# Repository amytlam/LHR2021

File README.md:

# LHR2021
This is the repository for the files associated with the paper "DIY Liquid Handling Robots for Integrated STEM Education and Life-Science Research".

This includes the following:
1. Hardware documentation:
    - Parts list
    - CAD source designs for mechanical parts
    - Laser cutting fabrication files (5 sheets)
    - Fabrication files for 3D printed parts
    - Electronic circuit schematic diagrams and CAD files
    - Assembly instructions
2. Software:
    - Low-level control software for Arduino
    - Python API and tools for tuning and calibration
    - Snap4Arduino visual programming environment

## Contents

The `hardware/` directory of this repository contains fabrication files and documentation for all hardware for the three-axis robot. CAD source designs for the mechanical components and subassemblies of the robot can be found in an associated [Onshape project](https://cad.onshape.com/documents/6f3ff9e60612f07463807b51/w/7c9831bb106114d48918156b/e/005c0d1900650c2e45e341be?renderMode=0&uiState=6254cec2aa34676ff2f642a7), which is made public for copying and exporting. These source designs were exported to create the cut patterns in `hardware/laser_cut_CAD_files/` and the 3D printing files in `hardware/3d_printed_CAD_files/`.

Source code and overview-level documentation of all software can be found at the associated repository [github.com/ethanjli/liquid-handling-robotics](https://github.com/ethanjli/liquid-handling-robotics).

## Usage

This hardware was developed and tested until October 2018 and is not currently maintained or supported. Troubleshooting and extensive technical skills will be needed to independently replicate the hardware design from the documentation provided in this repository, requiring deep familiarity with laser cutting, 3-D printing, assembly of simple printed circuit boards, and circuit prototyping.

### Mechanical Fabrication

Laser-cut parts, collected in the `hardware/laser_cut_CAD_files/annotated_laser_cutting_pdf_files.zip` file, are designed for 1/8-inch thick acrylic plates. Due to kerf and thickness variations among laser cutters and acrylic plates, the laser cutting patterns may need to be manually re-exported from the Onshape CAD source project after modifying the `kerfAdjustment` FeatureScript variable in the [`Design Parameters/Acrylic` tab](https://cad.onshape.com/documents/6f3ff9e60612f07463807b51/w/7c9831bb106114d48918156b/e/27868389b7af3fd50301f4c9) of the project.

Two units of the magnet hub, used in the x- and y-axis linear actuators of the robot, will need to be 3D printed using the `hardware/3d_printed_CAD_files/Magnet Hub (in).stl` file or the `hardware/3d_printed_CAD_files/Magnet Hub (mm).stl` file, depending on the length units used by the 3D printer. 

### Mechanical Assembly

Mechanical assembly can be performed following the photographs and notes in the `hardware/assembly_instructions/LHR Assembly of Laser Cut Parts.pdf` file.

Additionally, an 8mm x 2.50mm magnet, listed in the bill of materials, will need to be inserted into each 3D-printed magnet hub, and a magnet hub should be press-fitted to the D-shaped output shaft of the motor for each of the x- and y-axis linear actuators. A magnetic angle sensor printed circuit board (described below) should then be mounted to the linear actuator so that the angle sensor contacts the magnet.

### Circuit Assembly

The printed circuit board for the magnetic angle sensor, used in the x- and y-axis linear actuators of the robot, will need to be fabricated and assembled. Eagle CAD files and a zip archive of Gerber files can be found inside `hardware/electronic_circuits`, with filename `LHR Mag Sensor Mk2`.

For I2C switching of the magnetic angle sensor boards, a simple MOSFET circuit will need to be assembled (e.g. on a breadboard) from the schematic shown in the `hardware/electronic_circuits/LHR Circuit Diagrams.pdf` file.

Wiring and pin connections for the Arduino are shown in the `hardware/electronic_circuits/LHR Circuit Diagrams.pdf` file. Note that wires for the I2C signal lines must be kept as short as possible in order to mitigate radio frequency interference on those wires, which manifests as freezes in the Arduino software requiring a hard reset of the Arduino.

### Software Usage

Instructions for software setup and usage can be found in the README for [github.com/ethanjli/liquid-handling-robotics](https://github.com/ethanjli/liquid-handling-robotics#readme)

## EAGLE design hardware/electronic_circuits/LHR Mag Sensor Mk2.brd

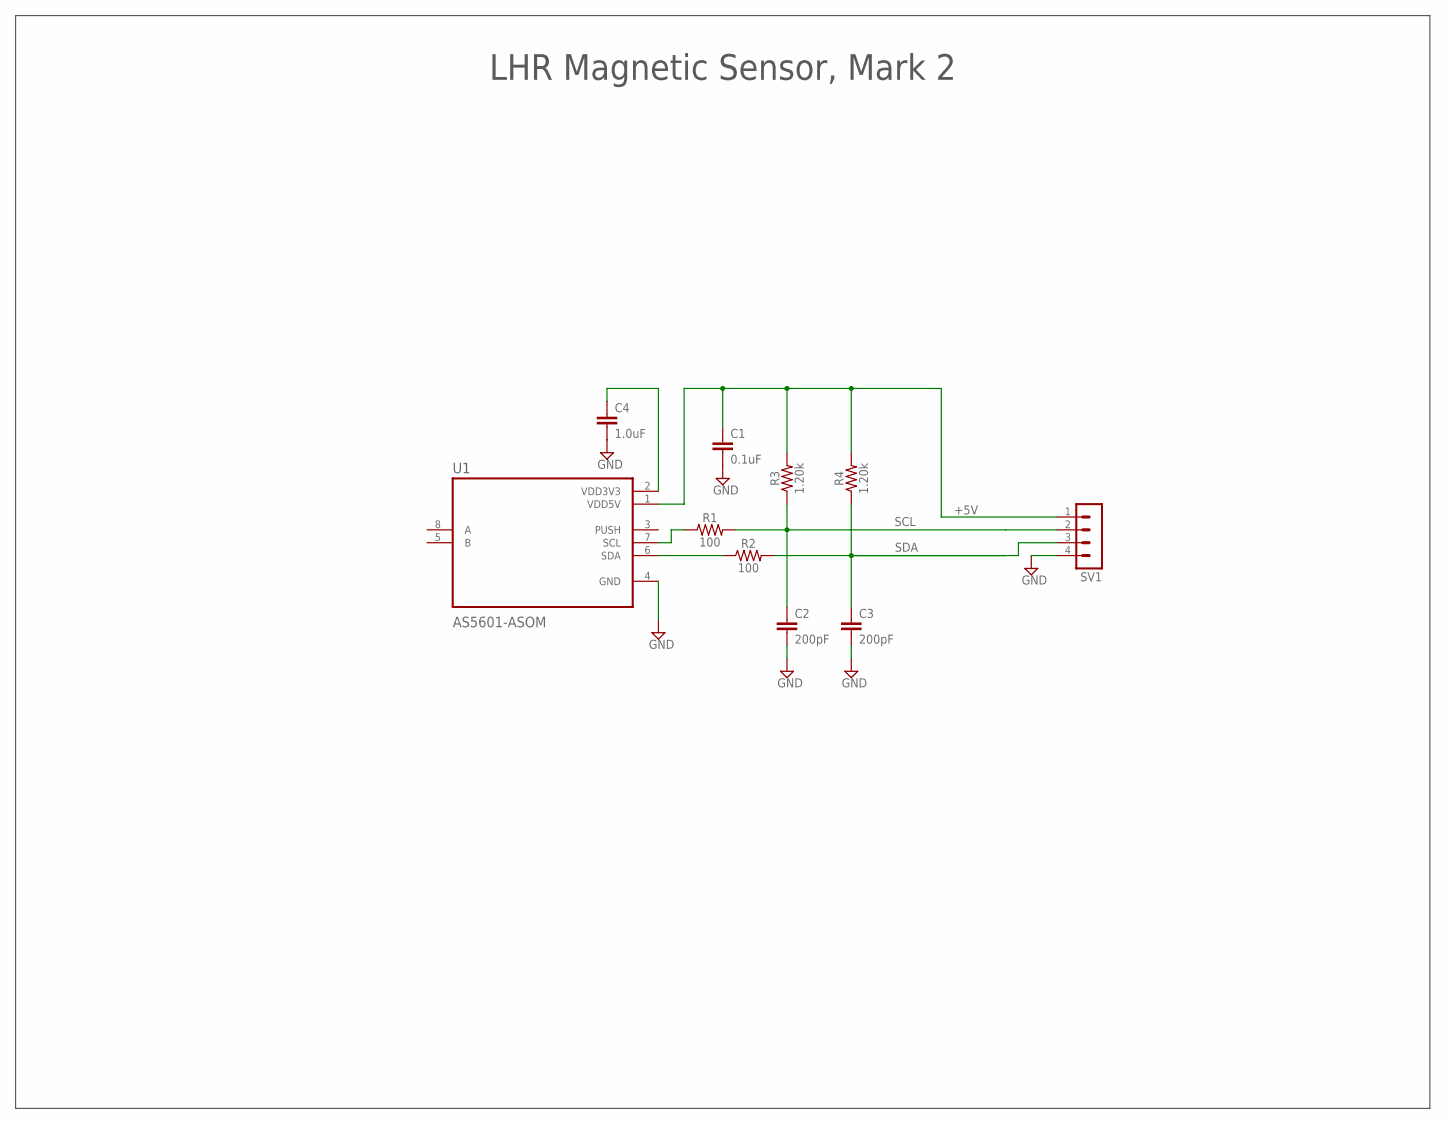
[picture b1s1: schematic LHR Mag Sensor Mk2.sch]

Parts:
C1: 0.1uF; 0603
C2, C3: 200pF; 0603
C4: 1.0uF; 0603
R1, R2: 100; 0603
R3, R4: 1.20k; 0603
SV1: MA04-1
U1: AS5601-ASOM; SOIC127P600X172-8N

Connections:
+5V: C1.1, R3.2, R4.2, SV1.1, U1.1 (VDD5V)
GND: C1.2, C2.2, C3.2, C4.2, SV1.4, U1.4 (GND)
unnamed: R2.1, U1.6 (SDA)
unnamed: C4.1, U1.2 (VDD3V3)
unnamed: R1.1, U1.7 (SCL)
SCL: C2.1, R1.2, R3.1, SV1.2
SDA: C3.1, R2.2, R4.1, SV1.3

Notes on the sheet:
LHR Magnetic Sensor, Mark 2

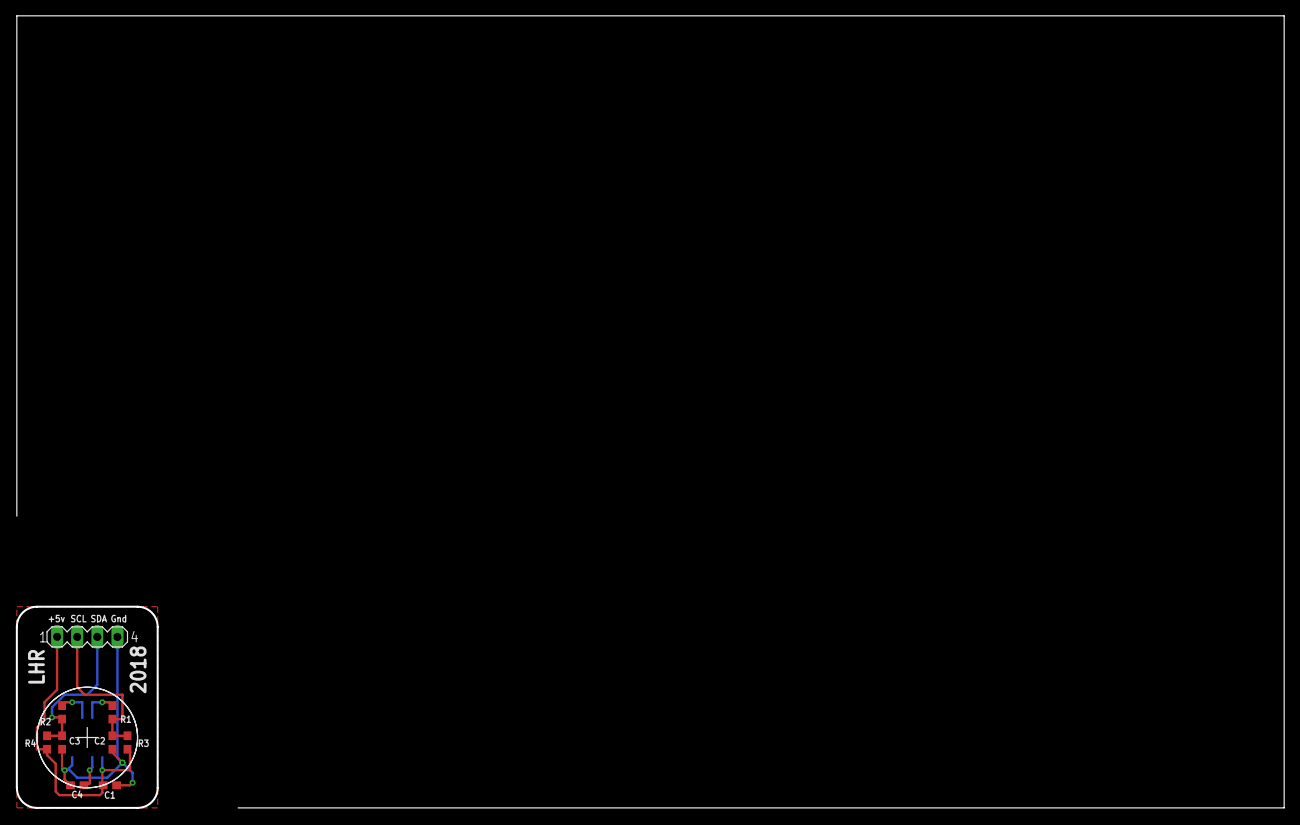
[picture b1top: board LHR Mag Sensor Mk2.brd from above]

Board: 2 copper layers, 160.0 x 100.0 mm, 10 parts (1 on the bottom side), 7 nets.

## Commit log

2021-04-20 Add first set of files
2022-04-12 Add more information to the README, add 3D printing files
2022-04-12 Fix typo, adjust framing
2022-04-12 Add CAD and fab files for the angle sensor PCB

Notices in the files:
parts and their libraries:
SparkFun-Capacitors: Licensing: Creative Commons ShareAlike 4.0 International - https://creativecommons.org/licenses/by-sa/4.0
